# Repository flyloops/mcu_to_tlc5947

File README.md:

# mcu_to_tlc5947 
A simple PCB for connecting an Arduino (Teensy or Nano) to the Adafruit TLC5947 PWM LED Driver. In progress. 

* [Teensy schematic (PDF)](teensy/mcu_to_tlc5947.pdf)
* [Teensy bill-of-materials](teensy/BOM.txt)

# Top View: 

# Bottom View:

# License: 
Creative Commons Attribution 4.0 International CC BY 4.0

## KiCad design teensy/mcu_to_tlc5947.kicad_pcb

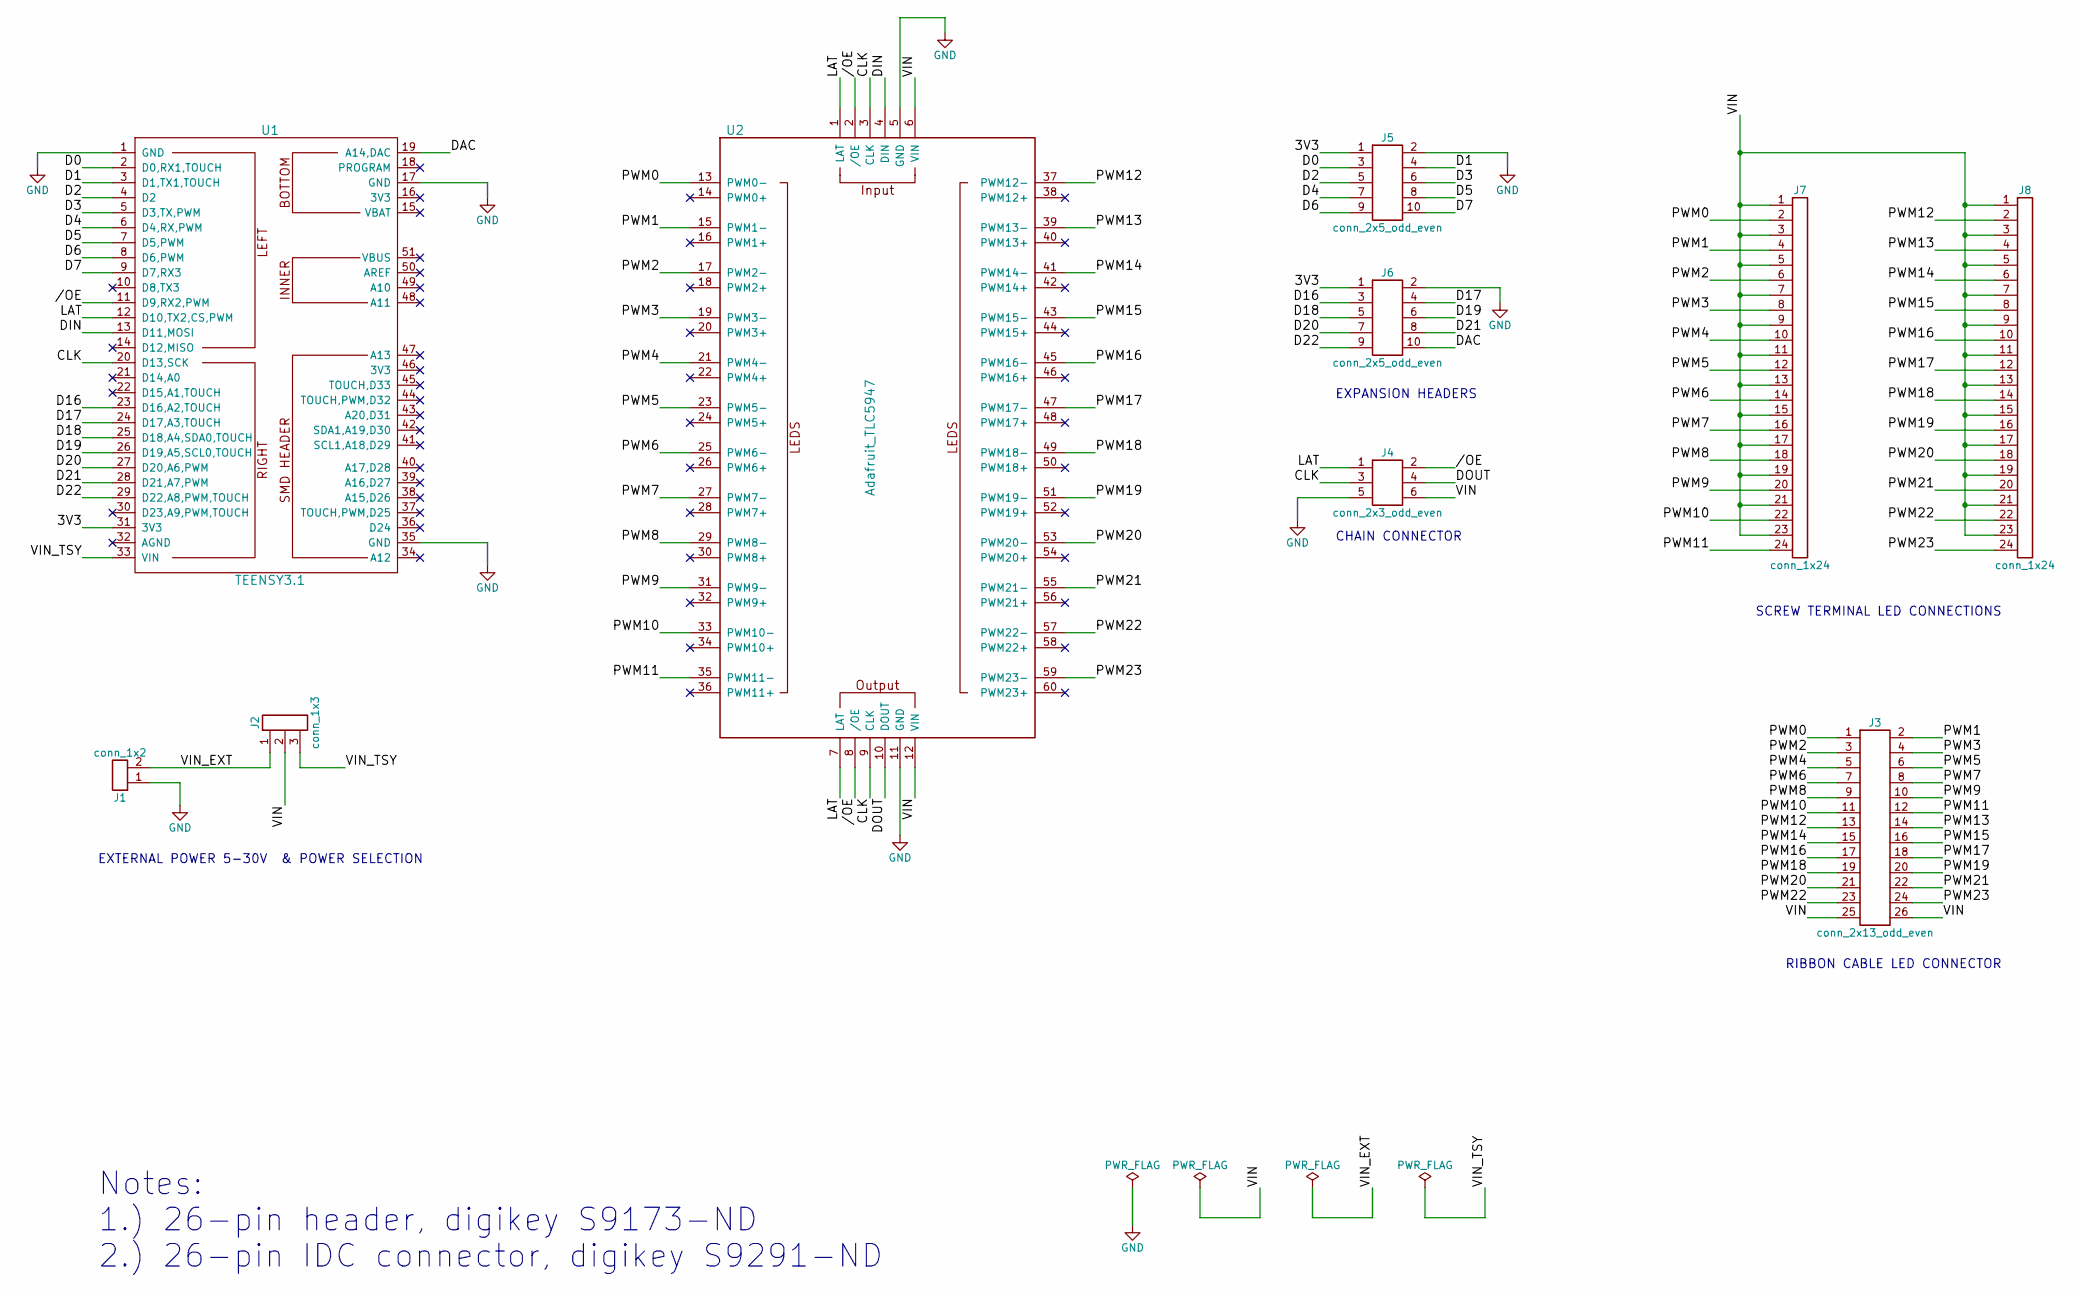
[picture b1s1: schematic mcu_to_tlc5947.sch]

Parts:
J1: conn_1x2; BLOCK_CONN_2X1
J2: conn_1x3; PIN_ARRAY_1X3
J3: conn_2x13_odd_even; 5X2_SHRD_HEADER
J4: conn_2x3_odd_even; 3X2_SHRD_HEADER
J5, J6: conn_2x5_odd_even; 5X2_SHRD_HEADER
J7, J8: conn_1x24; BLOCK_CONN_2X1
U1: TEENSY3.1; TEENSY3X
U2: Adafruit_TLC5947

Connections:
/3V3: J5.1, J6.1, U1.31 (3V3)
//OE: J4.2, U1.11 (D9,RX2,PWM), U2.2 (/OE), U2.8 (/OE)
/CLK: J4.3, U1.20 (D13,SCK), U2.3 (CLK), U2.9 (CLK)
/D0: J5.3, U1.2 (D0,RX1,TOUCH)
/D1: J5.4, U1.3 (D1,TX1,TOUCH)
/D2: J5.5, U1.4 (D2)
/D3: J5.6, U1.5 (D3,TX,PWM)
/D4: J5.7, U1.6 (D4,RX,PWM)
/D5: J5.8, U1.7 (D5,PWM)
/D6: J5.9, U1.8 (D6,PWM)
/D7: J5.10, U1.9 (D7,RX3)
/D16: J6.3, U1.23 (D16,A2,TOUCH)
/D17: J6.4, U1.24 (D17,A3,TOUCH)
/D18: J6.5, U1.25 (D18,A4,SDA0,TOUCH)
/D19: J6.6, U1.26 (D19,A5,SCL0,TOUCH)
/D20: J6.7, U1.27 (D20,A6,PWM)
/D21: J6.8, U1.28 (D21,A7,PWM)
/D22: J6.9, U1.29 (D22,A8,PWM,TOUCH)
/DAC: J6.10, U1.19 (A14,DAC)
/DIN: U1.13 (D11,MOSI), U2.4 (DIN)
/DOUT: J4.4, U2.10 (DOUT)
/LAT: J4.1, U1.12 (D10,TX2,CS,PWM), U2.1 (LAT), U2.7 (LAT)
/PWM0: J3.1, J7.2, U2.13 (PWM0-)
/PWM1: J3.2, J7.4, U2.15 (PWM1-)
/PWM2: J3.3, J7.6, U2.17 (PWM2-)
/PWM3: J3.4, J7.8, U2.19 (PWM3-)
/PWM4: J3.5, J7.10, U2.21 (PWM4-)
/PWM5: J3.6, J7.12, U2.23 (PWM5-)
/PWM6: J3.7, J7.14, U2.25 (PWM6-)
/PWM7: J3.8, J7.16, U2.27 (PWM7-)
/PWM8: J3.9, J7.18, U2.29 (PWM8-)
/PWM9: J3.10, J7.20, U2.31 (PWM9-)
/PWM10: J3.11, J7.22, U2.33 (PWM10-)
/PWM11: J3.12, J7.24, U2.35 (PWM11-)
/PWM12: J3.13, J8.2, U2.37 (PWM12-)
/PWM13: J3.14, J8.4, U2.39 (PWM13-)
/PWM14: J3.15, J8.6, U2.41 (PWM14-)
/PWM15: J3.16, J8.8, U2.43 (PWM15-)
/PWM16: J3.17, J8.10, U2.45 (PWM16-)
/PWM17: J3.18, J8.12, U2.47 (PWM17-)
/PWM18: J3.19, J8.14, U2.49 (PWM18-)
/PWM19: J3.20, J8.16, U2.51 (PWM19-)
/PWM20: J3.21, J8.18, U2.53 (PWM20-)
/PWM21: J3.22, J8.20, U2.55 (PWM21-)
/PWM22: J3.23, J8.22, U2.57 (PWM22-)
/PWM23: J3.24, J8.24, U2.59 (PWM23-)
/VIN: J2.2, J3.25, J3.26, J4.6, J7.1, J7.3, J7.5, J7.7, J7.9, J7.11, J7.13, J7.15, J7.17, J7.19, J7.21, J7.23, J8.1, J8.3, J8.5, J8.7, J8.9, J8.11, J8.13, J8.15, J8.17, J8.19, J8.21, J8.23, U2.6 (VIN), U2.12 (VIN)
/VIN_EXT: J1.2, J2.1
/VIN_TSY: J2.3, U1.33 (VIN)
GND: J1.1, J4.5, J5.2, J6.2, U1.1 (GND), U1.17 (GND), U1.35 (GND), U2.5 (GND), U2.11 (GND)

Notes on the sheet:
CHAIN CONNECTOR
EXTERNAL POWER 5-30V & POWER SELECTION
SCREW TERMINAL LED CONNECTIONS
RIBBON CABLE LED CONNECTOR
EXPANSION HEADERS
Notes: 1.) 26-pin header, digikey S9173-ND 2.) 26-pin IDC connector, digikey S9291-ND

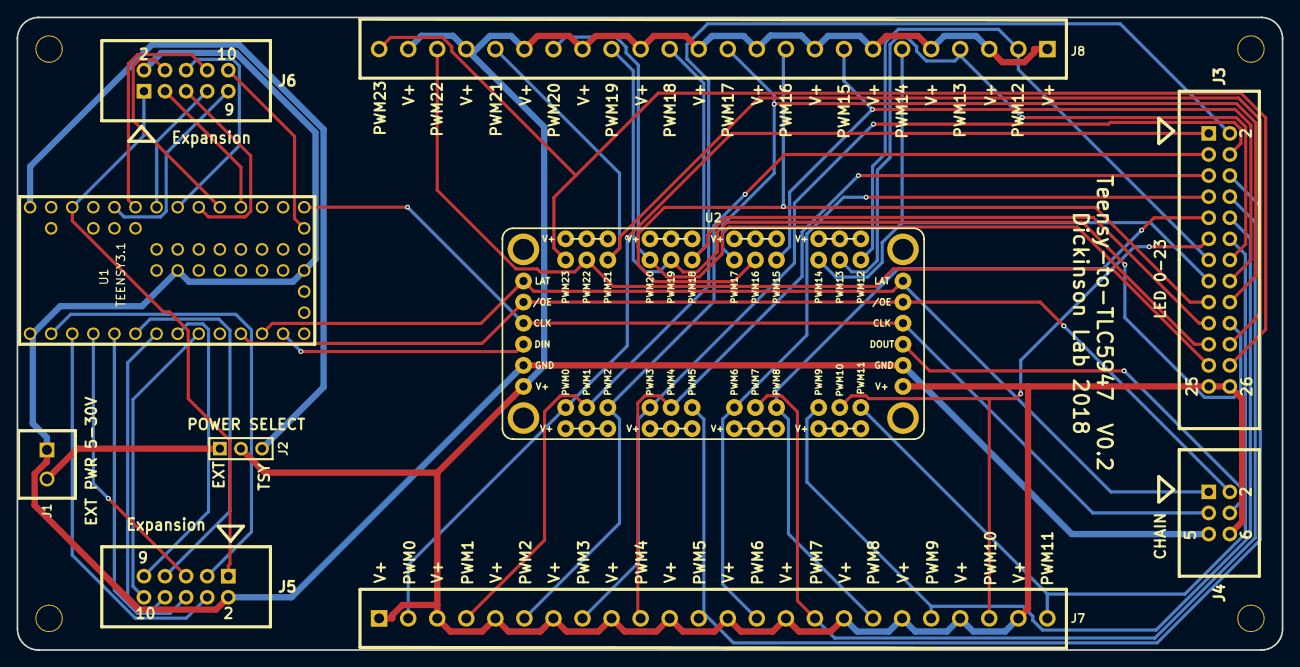
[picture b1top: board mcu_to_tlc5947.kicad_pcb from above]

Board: 2 copper layers, 152.4 x 76.2 mm, 14 parts (0 on the bottom side), 50 nets.

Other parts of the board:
M1, M2, M3, M4: VAL**; MOUNT_HOLE_4_40

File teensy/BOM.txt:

Components
##########

Part        Description                  Package      Vendor     Part Number                   Qty
----        -----------                  -------      ------     -----------                   ---
J1,J7,J8    terminal block, 2-pos        custom       Digikey    ED2635-ND                     25
J2          break away header 0.1"       NA           Digikey    S1011EC-40-ND                 1
J3          13x2 shrouhded header        NA           Digikey    S9173-ND                      1 
J4          3x2 shrouded header          NA           Digikey    732-5394-ND                   1
J5,J6       5x2 shrouded header          NA           Digikey    S9169-ND                      2
U1          Teensy 3.2 dev board         custom       PJRC       teensy 3.2                    1
U2          Adafruit 24-Chan LED driver  custom       Adafruit   1429                          1    
            3x2 male header              NA           Digikey    609-3234-ND                   8 
            3x2 female header            NA           Digikey    609-6001-ND                   8
            6x1 female header            NA           Digikey    S7004-ND                      2
            break away header 0.1"       NA           Digikey    S1011EC-40-ND                 1


Accessories
###########

Description                                Vendor     Part Number                   Qty
-----------                                ------     -----------                   ---
3x2 IDC cable connector                    Digikey    732-5394-ND                   2
5x2 IDC cable connector                    Digieky    S9306-ND                      2
13x2 IDC cable connector                   Digikey    S9291-ND                      2
26 conductor ribbon cable 0.005" pitch     Digikey    AE26G-5-ND                    1 (5')

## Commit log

2018-11-17 Project creation.
2018-11-20 Completed initial version of design. Created version 0.1 gerber files.
2018-11-26 Added BOM.
2018-11-27 Added missing parts to BOM and added pdf of schematic.
2018-11-27 Added images and updated readme.
2018-11-27 Fixed caps issue in readme.
2018-12-08 Fixed error with adafruit tlc5947 foot print.
2018-12-21 Update the pcb images.
